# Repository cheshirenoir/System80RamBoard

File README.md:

# System80RamBoard
It's a super simple 32k RAM expansion for the System 80
COMPLETELY UNTESTED AS YET

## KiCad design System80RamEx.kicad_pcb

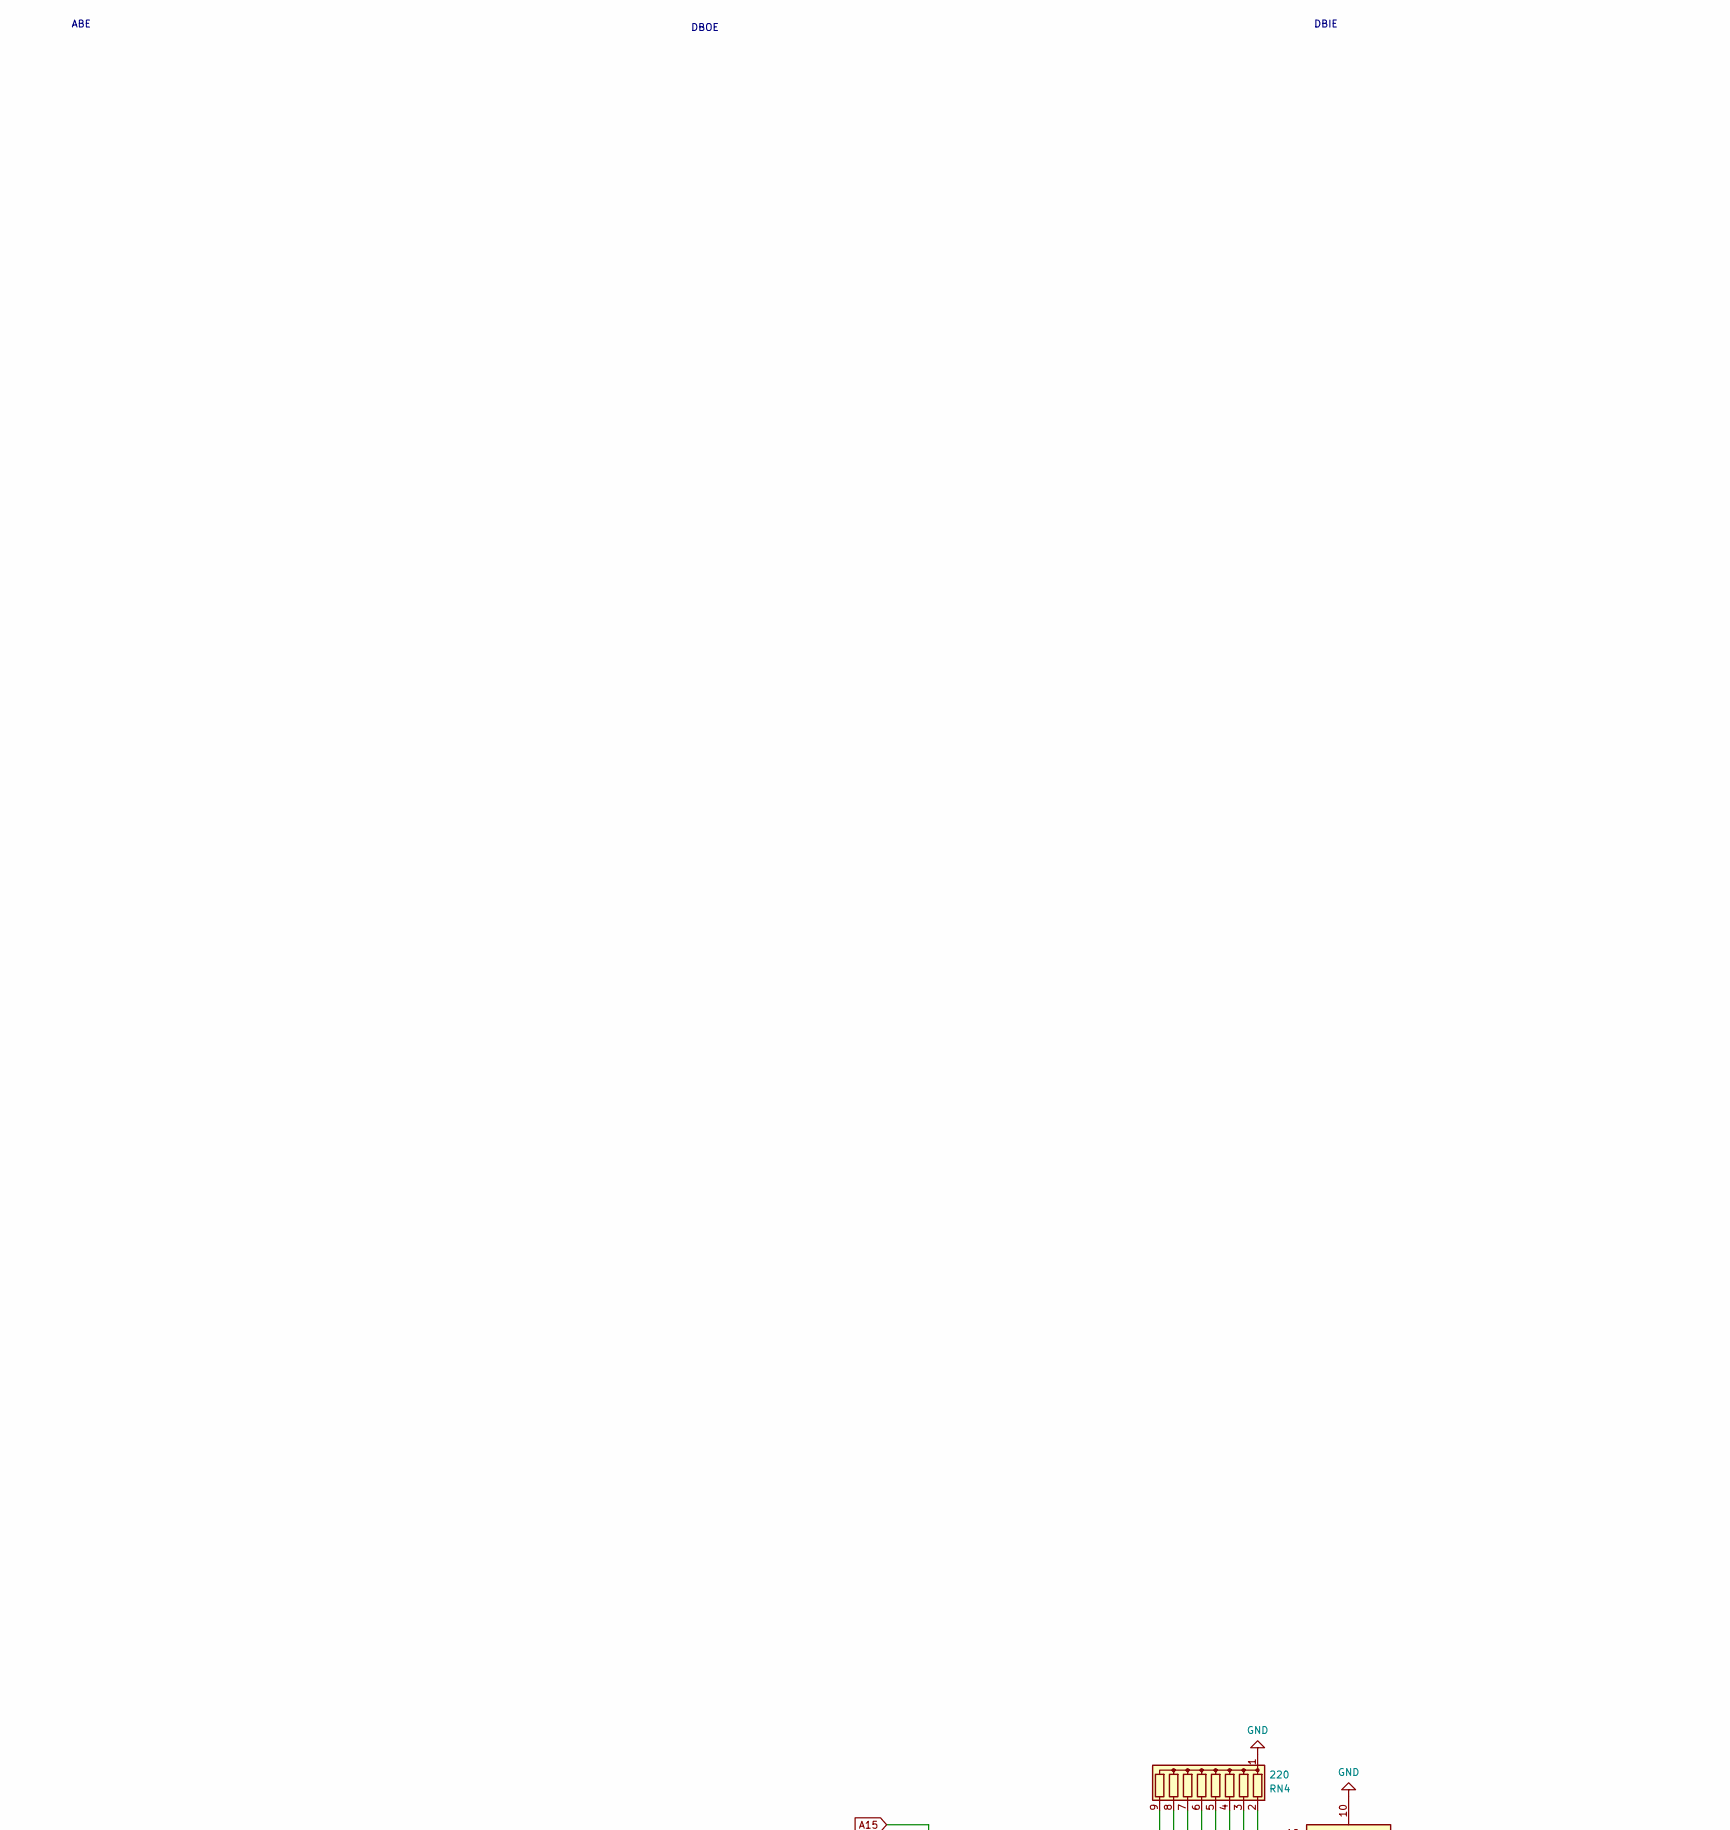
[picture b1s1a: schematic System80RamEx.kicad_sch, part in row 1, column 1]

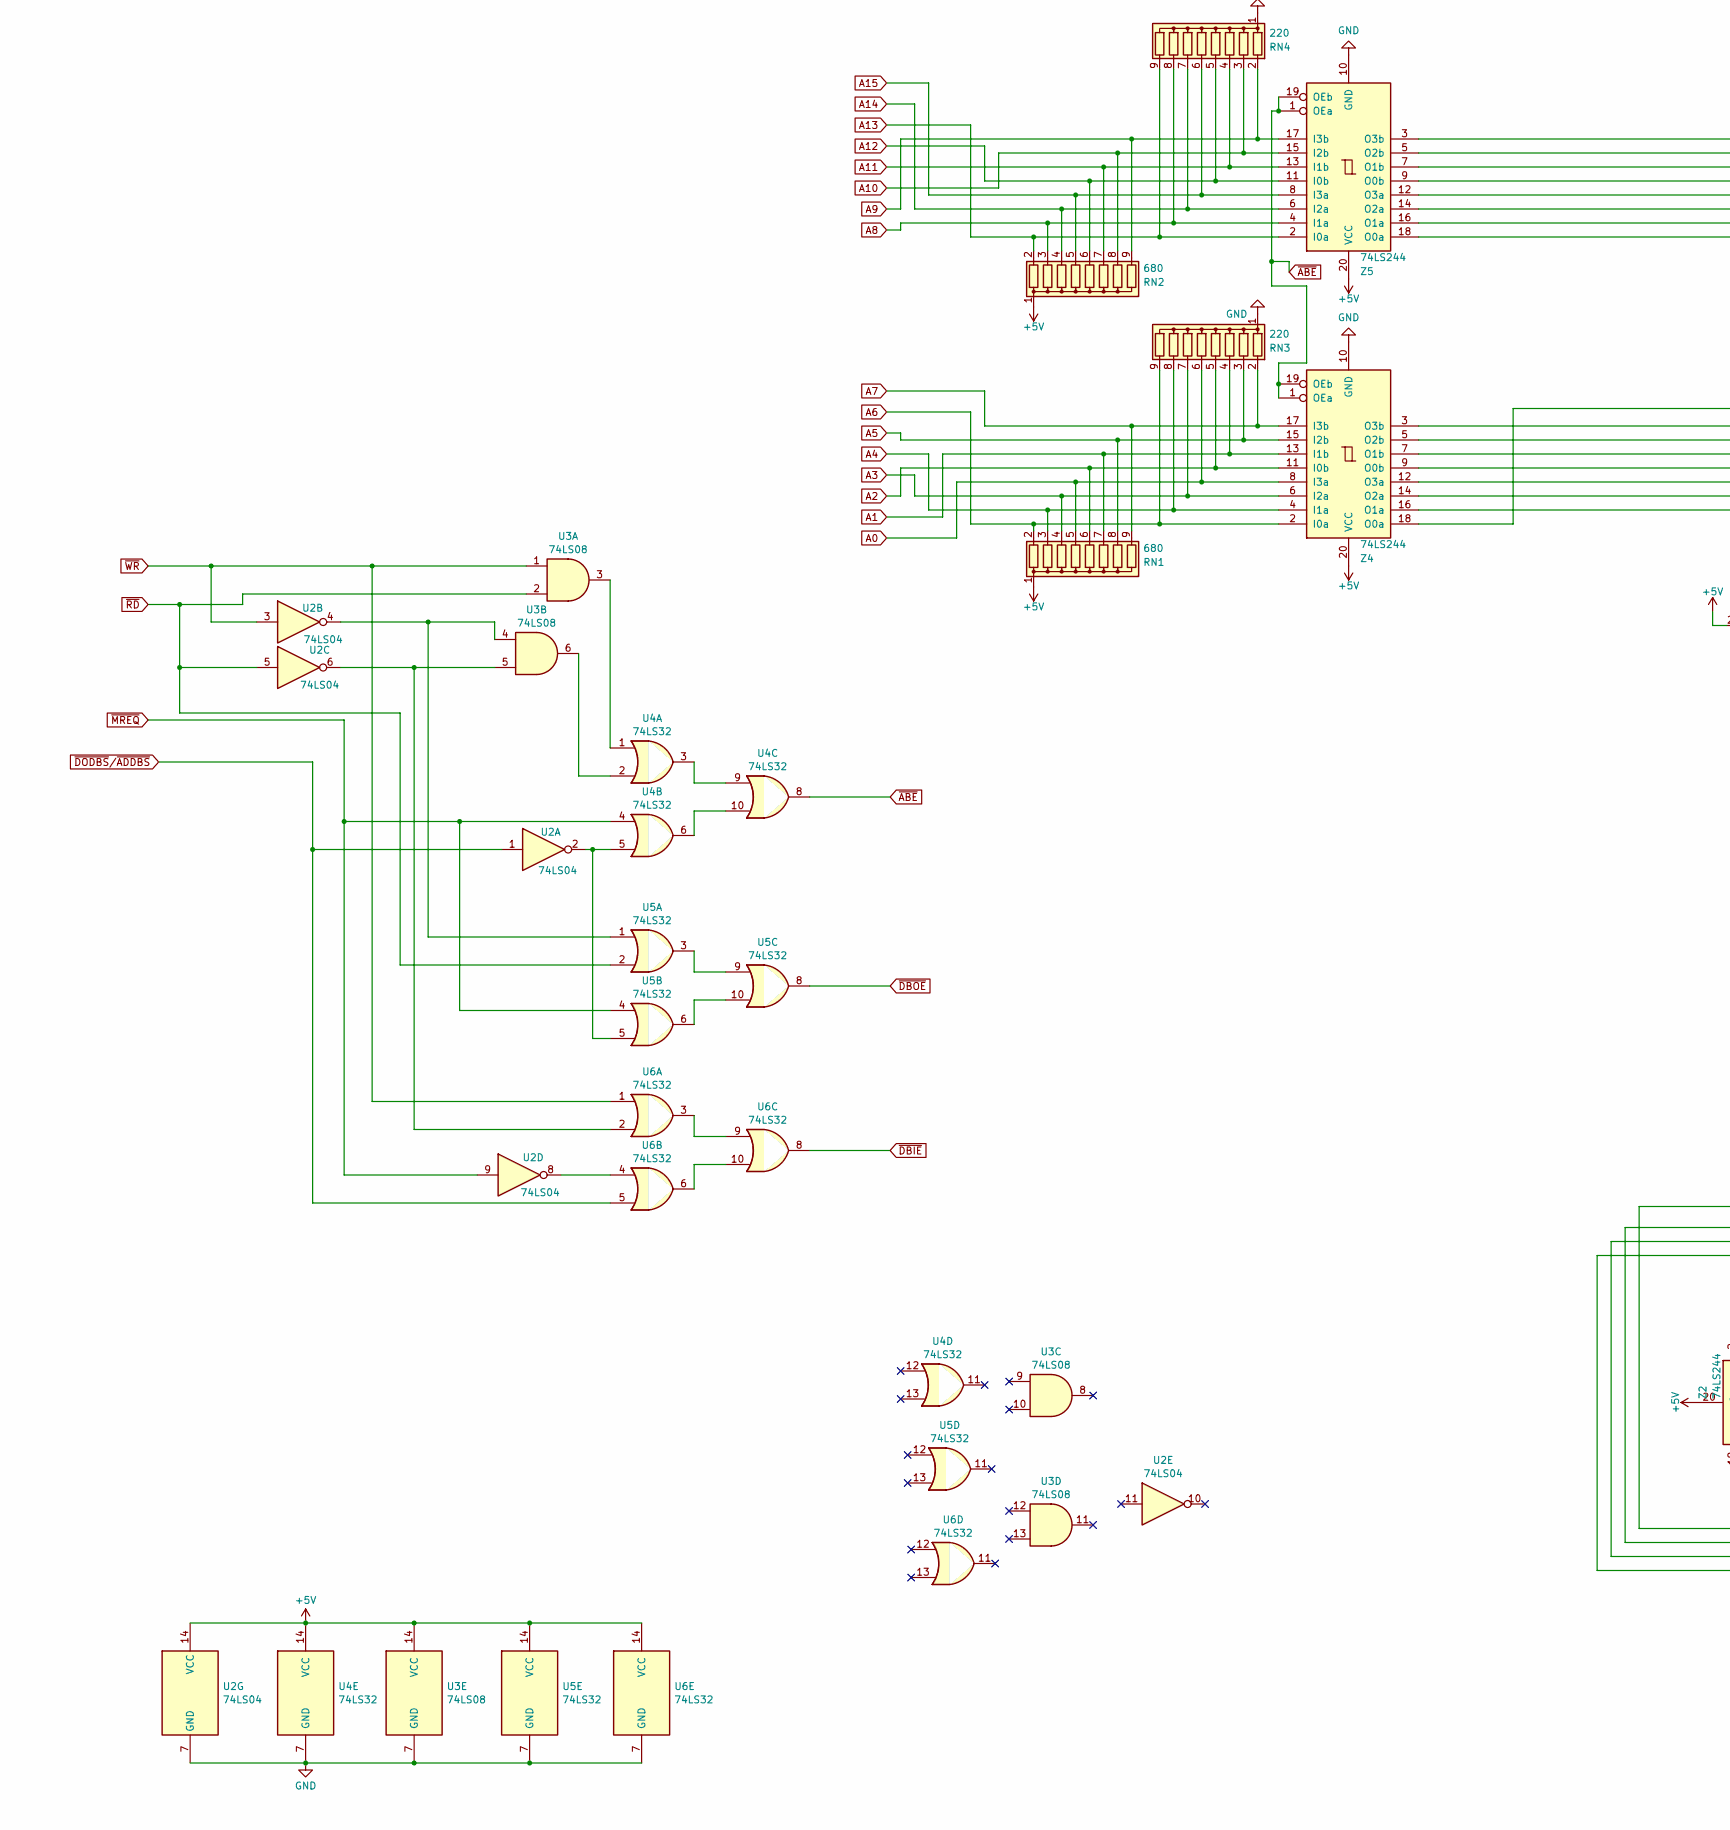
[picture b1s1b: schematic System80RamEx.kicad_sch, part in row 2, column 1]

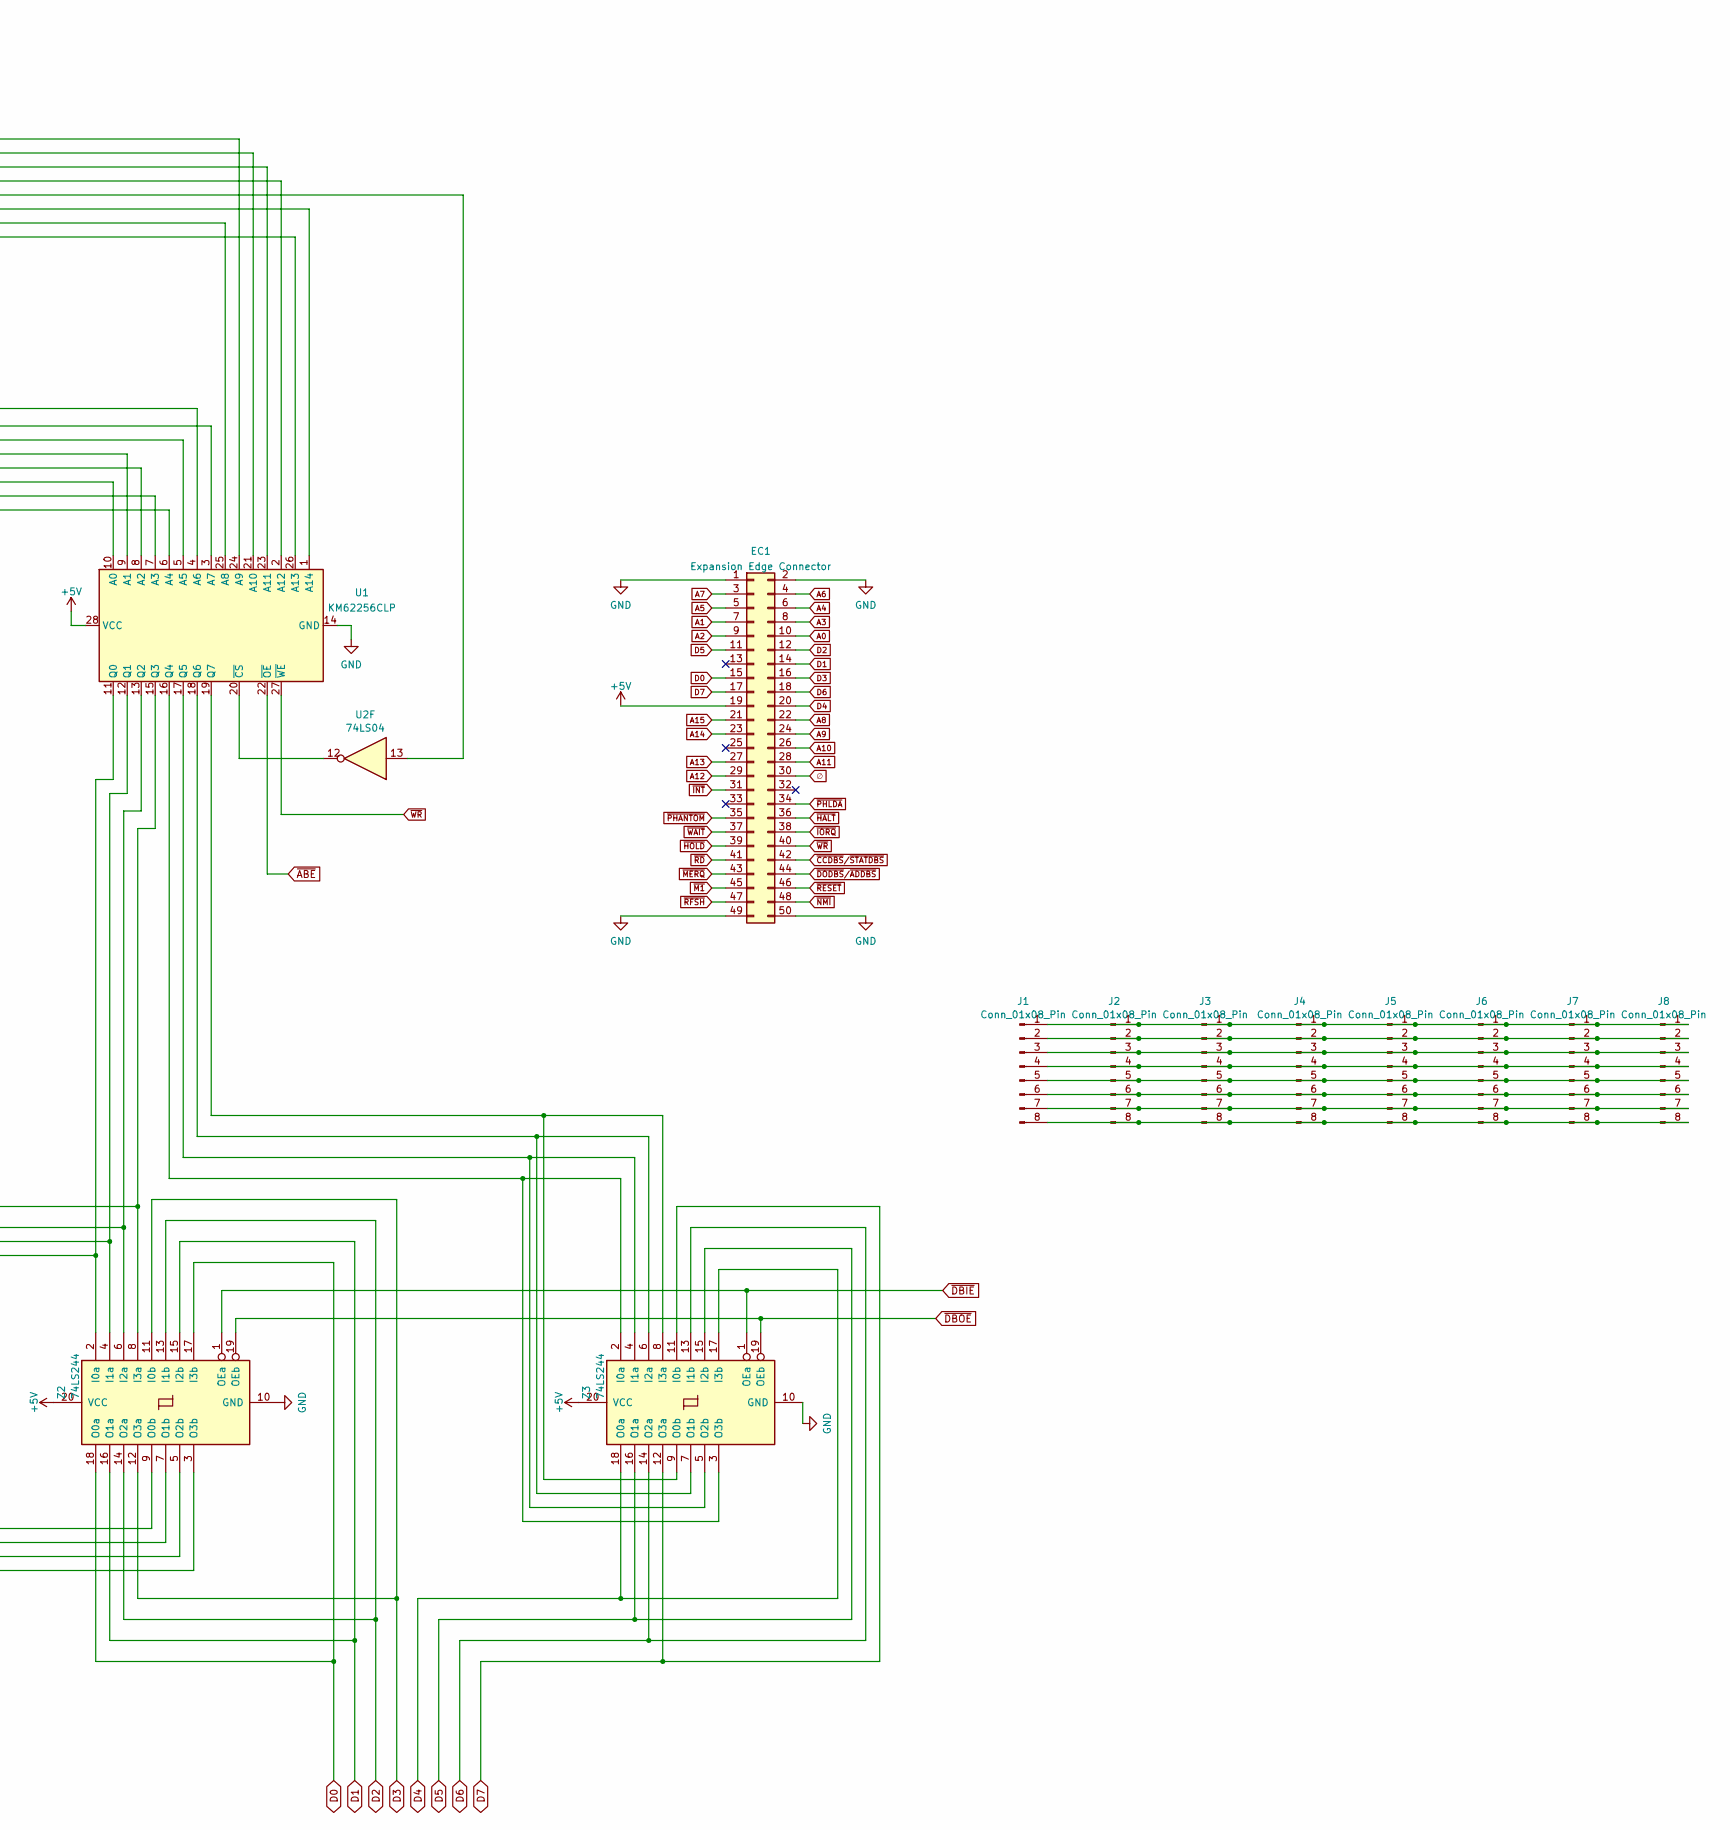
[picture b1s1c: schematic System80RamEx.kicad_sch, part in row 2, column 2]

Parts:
EC1: Expansion Edge Connector; 50 pin card edge connector
J1, J2, J3, J4, J5, J6, J7, J8: Conn_01x08_Pin; PinHeader_1x08_P2.54mm_Vertical
RN1, RN2: 680; R_Array_SIP9
RN3, RN4: 220; R_Array_SIP9
U1: KM62256CLP; DIP-28_W15.24mm
U2: 74LS04; DIP-14_W7.62mm_LongPads
U3: 74LS08; DIP-14_W7.62mm_LongPads
U4, U5, U6: 74LS32; DIP-14_W7.62mm_LongPads
Z2, Z3, Z4, Z5: 74LS244; DIP-20_W7.62mm_LongPads

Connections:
+5V: EC1.19, RN1.1 (common), RN2.1 (common), U1.28 (VCC), U2.14 (VCC), U3.14 (VCC), U4.14 (VCC), U5.14 (VCC), U6.14 (VCC), Z2.20 (VCC), Z3.20 (VCC), Z4.20 (VCC), Z5.20 (VCC)
A0: EC1.10, RN1.5 (R4), RN3.6 (R5), Z4.8 (I3a)
A1: EC1.7, RN1.7 (R6), RN3.4 (R3), Z4.13 (I1b)
A2: EC1.9, RN1.6 (R5), RN3.5 (R4), Z4.11 (I0b)
A3: EC1.8, RN1.4 (R3), RN3.7 (R6), Z4.6 (I2a)
A4: EC1.6, RN1.3 (R2), RN3.8 (R7), Z4.4 (I1a)
A5: EC1.5, RN1.8 (R7), RN3.3 (R2), Z4.15 (I2b)
A6: EC1.4, RN1.2 (R1), RN3.9 (R8), Z4.2 (I0a)
A7: EC1.3, RN1.9 (R8), RN3.2 (R1), Z4.17 (I3b)
A8: EC1.22, RN2.3 (R2), RN4.8 (R7), Z5.4 (I1a)
A9: EC1.24, RN2.9 (R8), RN4.2 (R1), Z5.17 (I3b)
A10: EC1.26, RN2.8 (R7), RN4.3 (R2), Z5.15 (I2b)
A11: EC1.28, RN2.7 (R6), RN4.4 (R3), Z5.13 (I1b)
A12: EC1.29, RN2.6 (R5), RN4.5 (R4), Z5.11 (I0b)
A13: EC1.27, RN2.2 (R1), RN4.9 (R8), Z5.2 (I0a)
A14: EC1.23, RN2.4 (R3), RN4.7 (R6), Z5.6 (I2a)
A15: EC1.21, RN2.5 (R4), RN4.6 (R5), Z5.8 (I3a)
D0: EC1.15, Z2.17 (I3b), Z2.18 (O0a)
D1: EC1.14, Z2.15 (I2b), Z2.16 (O1a)
D2: EC1.12, Z2.13 (I1b), Z2.14 (O2a)
D3: EC1.16, Z2.11 (I0b), Z2.12 (O3a)
D4: EC1.20, Z3.17 (I3b), Z3.18 (O0a)
D5: EC1.11, Z3.15 (I2b), Z3.16 (O1a)
D6: EC1.18, Z3.13 (I1b), Z3.14 (O2a)
D7: EC1.17, Z3.11 (I0b), Z3.12 (O3a)
GND: EC1.1, EC1.2, EC1.49, EC1.50, RN3.1 (common), RN4.1 (common), U1.14 (GND), U2.7 (GND), U3.7 (GND), U4.7 (GND), U5.7 (GND), U6.7 (GND), Z2.10 (GND), Z3.10 (GND), Z4.10 (GND), Z5.10 (GND)
unnamed: J1.1, J2.1, J3.1, J4.1, J5.1, J6.1, J7.1, J8.1
unnamed: J1.2, J2.2, J3.2, J4.2, J5.2, J6.2, J7.2, J8.2
unnamed: J1.3, J2.3, J3.3, J4.3, J5.3, J6.3, J7.3, J8.3
unnamed: J1.4, J2.4, J3.4, J4.4, J5.4, J6.4, J7.4, J8.4
unnamed: J1.5, J2.5, J3.5, J4.5, J5.5, J6.5, J7.5, J8.5
unnamed: J1.6, J2.6, J3.6, J4.6, J5.6, J6.6, J7.6, J8.6
unnamed: J1.7, J2.7, J3.7, J4.7, J5.7, J6.7, J7.7, J8.7
unnamed: J1.8, J2.8, J3.8, J4.8, J5.8, J6.8, J7.8, J8.8
unnamed: U1.10 (A0), Z4.12 (O3a)
unnamed: U1.9 (A1), Z4.7 (O1b)
unnamed: U1.8 (A2), Z4.9 (O0b)
unnamed: U1.7 (A3), Z4.14 (O2a)
unnamed: U1.6 (A4), Z4.16 (O1a)
unnamed: U1.5 (A5), Z4.5 (O2b)
unnamed: U1.4 (A6), Z4.18 (O0a)
unnamed: U1.3 (A7), Z4.3 (O3b)
unnamed: U1.25 (A8), Z5.16 (O1a)
unnamed: U1.24 (A9), Z5.3 (O3b)
unnamed: U1.21 (A10), Z5.5 (O2b)
unnamed: U1.23 (A11), Z5.7 (O1b)
unnamed: U1.2 (A12), Z5.9 (O0b)
unnamed: U1.26 (A13), Z5.18 (O0a)
unnamed: U1.1 (A14), Z5.14 (O2a)
unnamed: U1.11 (Q0), Z2.2 (I0a), Z2.3 (O3b)
unnamed: U1.12 (Q1), Z2.4 (I1a), Z2.5 (O2b)
unnamed: U1.13 (Q2), Z2.6 (I2a), Z2.7 (O1b)
unnamed: U1.15 (Q3), Z2.8 (I3a), Z2.9 (O0b)
unnamed: U1.16 (Q4), Z3.2 (I0a), Z3.3 (O3b)
unnamed: U1.17 (Q5), Z3.4 (I1a), Z3.5 (O2b)
unnamed: U1.18 (Q6), Z3.6 (I2a), Z3.7 (O1b)
unnamed: U1.19 (Q7), Z3.8 (I3a), Z3.9 (O0b)
unnamed: U1.20 (~CS), U2.12
unnamed: U2.2, U4.5, U5.5
unnamed: U2.4, U3.4, U5.1
unnamed: U2.6, U3.5, U6.2
unnamed: U2.8, U6.4
unnamed: U3.3, U4.1
unnamed: U3.6, U4.2
unnamed: U4.3, U4.9
unnamed: U4.6, U4.10
unnamed: U5.3, U5.9
unnamed: U5.6, U5.10
unnamed: U6.3, U6.9
unnamed: U6.6, U6.10
unnamed: U2.13, Z5.12 (O3a)
~ABE: U1.22 (~OE), U4.8, Z4.1 (OEa), Z4.19 (OEb), Z5.1 (OEa), Z5.19 (OEb)
~CCDBS/~STATDBS: EC1.42
~DBIE: U6.8, Z2.1 (OEa), Z3.1 (OEa)
~DBOE: U5.8, Z2.19 (OEb), Z3.19 (OEb)
~DODBS/~ADDBS: EC1.44, U2.1, U6.5
~HALT: EC1.36
~HOLD: EC1.39
~INT: EC1.31
~IORQ: EC1.38
~M1: EC1.45
~MERQ: EC1.43
~MREQ: U2.9, U4.4, U5.4
~NMI: EC1.48
~PHANTOM: EC1.35
~PHLDA: EC1.34
~RD: EC1.41, U2.5, U3.2, U5.2
~RESET: EC1.46
~RFSH: EC1.47
~WAIT: EC1.37
~WR: EC1.40, U1.27 (~WE), U2.3, U3.1, U6.1
∅: EC1.30

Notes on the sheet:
DBIE
LOGIC
ABE
DBOE

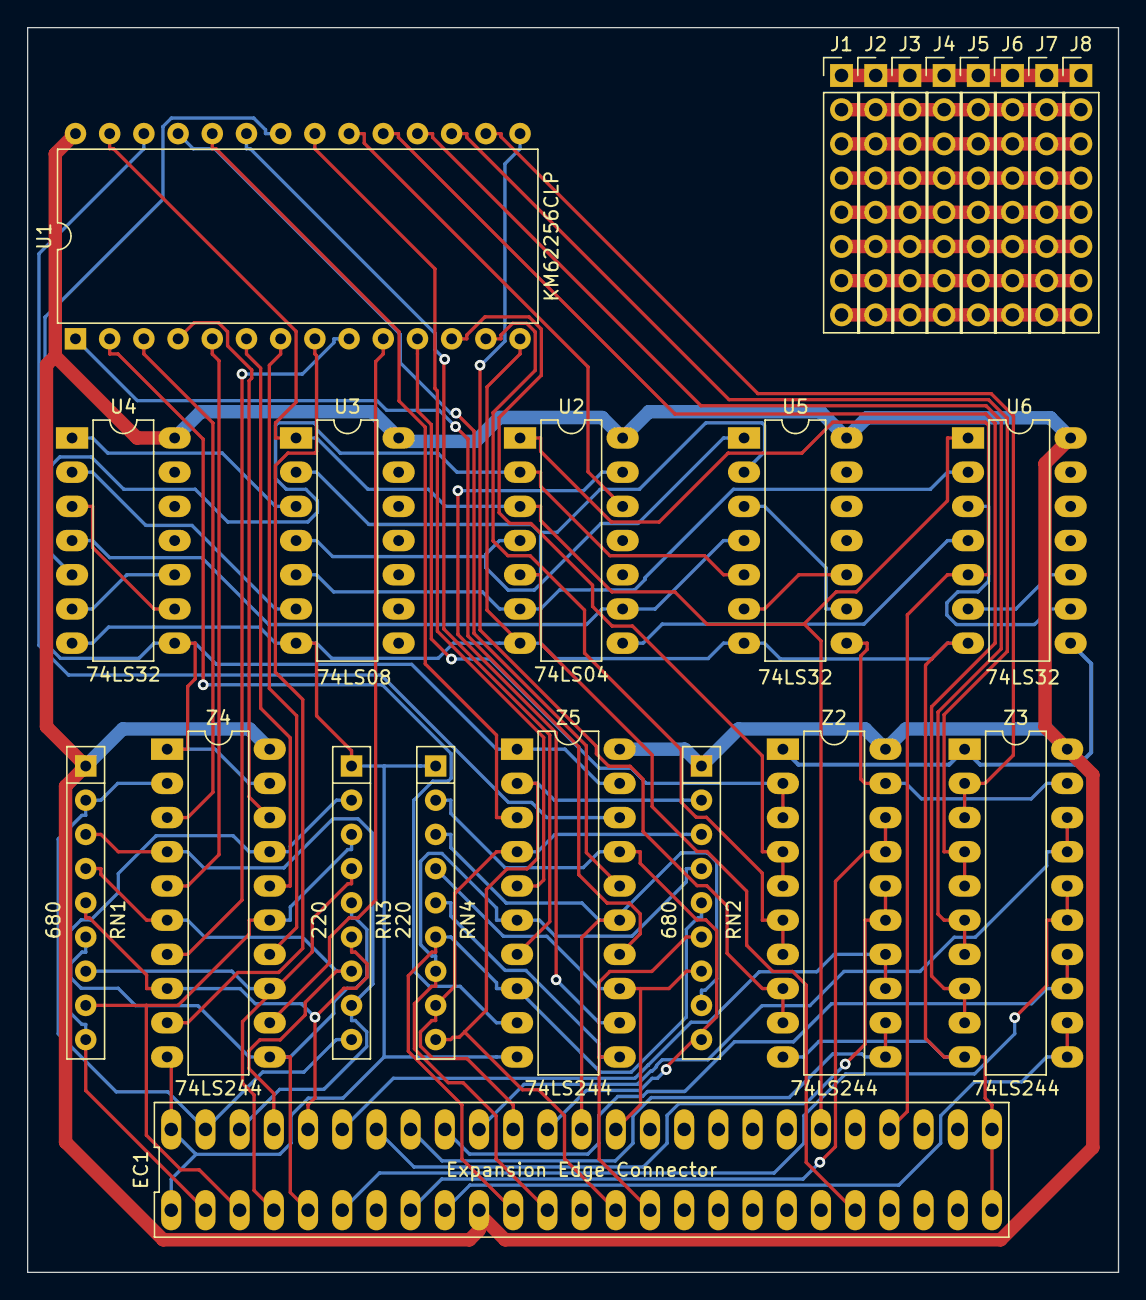
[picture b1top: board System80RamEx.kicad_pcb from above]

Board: 2 copper layers, 81.0 x 92.5 mm, 23 parts (0 on the bottom side), 78 nets.

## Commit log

2023-11-24 Add files via upload
    Cleaned up schematic
